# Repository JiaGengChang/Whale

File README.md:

# Whale Pro Micro

**Whale** is drop-in USB-C replacement for the sparkfun Pro Micro popular in split keyboards. It is a modified version of **[Goldfish]** by staticintlucas that uses a cheaply available USB-C receptacle. In Mandarin, goldfish sounds the same as whale.

Link to [Schematics]
Link to [PCB gerber files]

---

![Preview]

---

## Modifications to Goldfish

- PCB designed to fit cheap USB-C connector available on aliexpress **[usb-c-link]**.
- Reset switch that can be soldered on the back of the board (6mm by 2.5mm switch)**[switch-link]**.
- Different silkscreen text and art
- LED for power-source
---

## Disadvantages compared to other Goldfish-based boards

- Unlike **[Alvaro]**, it does not incorporate a fuse
- It also uses 0402 form factor capacitors and resistors, which is difficult to solder by hand
- No working boards tested!! (verdict will be out soon, watch this space)
---

## License

**[Creative Commons Attribution Share-Alike 4.0 License][License]**.

**-** Original `Arduino Mini` design by **Team Arduino**.

**-** Arduino `Pro Mini` design by **Spark Fun Electronics**.

**-** `Pro Micro` design by **Spark Fun Electronics**.

**-** Wiring schematics largely based on Goldfish by Dr Derivative.

---

<!----------------------------------------------------------------------------->

[Goldfish]: https://github.com/staticintlucas/Goldfish
[Schematics]: doc/whale.pdf
[PCB gerber files]: cad/gerbers/
[Preview]: doc/preview.png
[usb-c-link]: https://www.aliexpress.com/item/32998900371.html?spm=a2g0o.order_list.0.0.31b61802zlAvym
[switch-link]: https://www.aliexpress.com/item/1005002490728099.html?spm=a2g0o.order_list.0.0.4c182faewbHx
[Alvaro]: https://github.com/Ariamelon/Alvaro
[License]: https://creativecommons.org/licenses/by-sa/4.0/

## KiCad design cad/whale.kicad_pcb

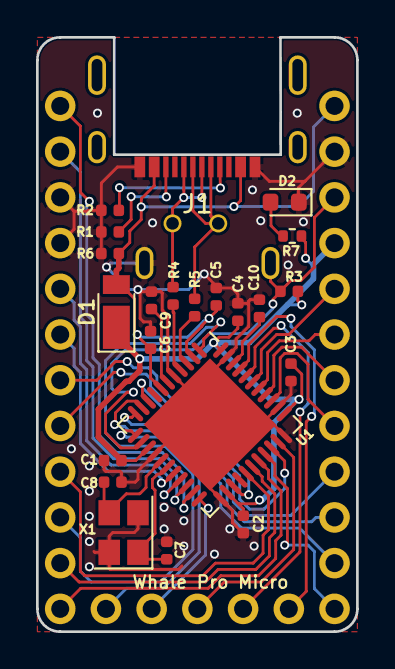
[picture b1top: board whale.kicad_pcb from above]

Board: 2 copper layers, 17.8 x 33.0 mm, 27 parts (0 on the bottom side), 38 nets.

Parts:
C1, C2, C3, C4, C5, C10: 0u1; C_0402_1005Metric
C6: 4u7; C_0402_1005Metric
C7, C8: 22p; C_0402_1005Metric
C9: 1u; C_0402_1005Metric
D1: D_Schottky; D_PowerDI-123
D2: LED_0603_1608Metric
J1: USB-C; 16p-mid-mount-1.6mm
J2: 01x02; Pins2
J3, J4: 01x12; Pins12
J5: 01x05; Pins5
R1, R2: 5k1; R_0402_1005Metric
R3, R6: 10k; R_0402_1005Metric
R4, R5: 22; R_0402_1005Metric
R7: R_0402_1005Metric
U1: ATmega32U4; QFN-44-1EP_7x7mm_P0.5mm_EP5.2x5.2mm
Whale ProMicro: LOGO; logo
X1: 16MHz; Crystal_SMD_SeikoEpson_FA238-4Pin_3.2x2.5mm

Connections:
/D+: J1.A6, J1.B6, J2.1, R4.2
/D-: J1.A7, J1.B7, J2.2, R5.2
/PB1: J3.9, U1.9
/PB2: J3.11, U1.10
/PB3: J3.10, U1.11
/PB4: J4.2, U1.28
/PB5: J4.1, U1.29
/PB6: J3.12, U1.30
/PB7: J5.5, U1.12
/PC6: J4.5, U1.31
/PC7: J5.3, U1.32
/PD0: J4.7, U1.18
/PD1: J4.8, U1.19
/PD2: J4.11, U1.20
/PD3: J4.12, U1.21
/PD4: J4.6, U1.25
/PD5: J5.4, U1.22
/PD7: J4.4, U1.27
/PE6: J4.3, U1.1
/PF0: J5.1, U1.41
/PF1: J5.2, U1.40
/PF4: J3.5, U1.39
/PF5: J3.6, U1.38
/PF6: J3.7, U1.37
/PF7: J3.8, U1.36
/RESET: J3.3, R3.1, U1.13
CC1: J1.A5, R2.2
CC2: J1.B5, R1.2
GND: C1.2, C2.2, C3.2, C4.2, C5.2, C6.2, C7.2, C8.2, C9.2, C10.2, D2.1, J1.A1, J3.2, J4.9, J4.10, R1.1, R2.1, R6.1, U1.5, U1.15, U1.23, U1.33, U1.35, U1.43, U1.45, X1.2, X1.4
LED: D2.2, R7.2
unnamed: C7.1, U1.17, X1.1
unnamed: C8.1, U1.16, X1.3
unnamed: C9.1, U1.6
unnamed: C10.1, U1.42
unnamed: R4.1, U1.4
unnamed: R5.1, U1.3
VBUS: C5.1, C6.1, D1.2, J1.A4, J3.1, R6.2, U1.2, U1.7
VCC: C1.1, C2.1, C3.1, C4.1, D1.1, J3.4, R3.2, R7.1, U1.14, U1.24, U1.34, U1.44

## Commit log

2022-05-15 Add preview image
2022-05-15 Fix README.md
2022-05-15 Edit README
2024-10-13 Create LICENSE

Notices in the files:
cad/whale.kicad_pcb:
Released under the Creative Commons Attribution Share-Alike 4.0 License
